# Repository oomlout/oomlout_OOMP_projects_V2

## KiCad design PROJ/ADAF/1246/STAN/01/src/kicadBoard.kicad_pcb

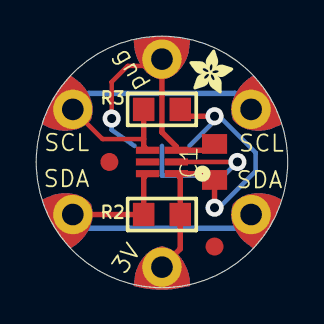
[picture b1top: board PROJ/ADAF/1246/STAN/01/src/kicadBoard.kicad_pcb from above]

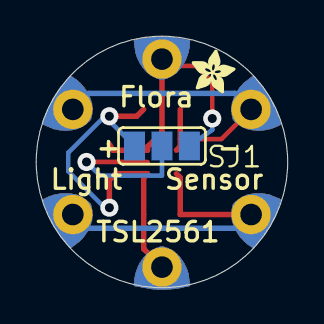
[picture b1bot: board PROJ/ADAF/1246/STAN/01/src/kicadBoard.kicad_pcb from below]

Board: 2 copper layers, 14.0 x 14.0 mm, 15 parts (2 on the bottom side), 5 nets.

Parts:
C1: 0.1uF; C0805K
FID1, FID2: FIDUCIAL""; FIDUCIAL_1MM
GND0: SEWTAP0.5IN; SEWINGTAP_0.5
R2, R3: 10K; _0805
SCL1, SCL2: SEWTAP0.5IN; SEWINGTAP_0.5
SDA1, SDA2: SEWTAP0.5IN; SEWINGTAP_0.5
SJ1: SJ_2
U2: TSL2561; TSL2561_FN
U$3, U$4: ADAFRUIT_2.5MM
VCC0: SEWTAP0.5IN; SEWINGTAP_0.5

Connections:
3.3V: C1.1, R2.2, R3.2, SJ1.3, U2.VDD, VCC0.TAP
ADDR: SJ1.2, U2.ADR
GND: C1.2, GND0.TAP, SJ1.1, U2.VSS
SCL: R3.1, SCL1.TAP, SCL2.TAP, U2.CLK
SDA: R2.1, SDA1.TAP, SDA2.TAP, U2.DATA

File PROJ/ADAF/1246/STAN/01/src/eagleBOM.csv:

"Part";"Value";"Device";"Package";"Description";"BOM";
"C1";"0.1uF";"C-USC0805K";"C0805K";"CAPACITOR, American symbol";"";
"FID1";"FIDUCIAL""";"FIDUCIAL""";"FIDUCIAL_1MM";"Fiducial Alignment Points";"EXCLUDE";
"FID2";"FIDUCIAL""";"FIDUCIAL""";"FIDUCIAL_1MM";"Fiducial Alignment Points";"EXCLUDE";
"GND";"SEWTAP0.5IN";"SEWTAP0.5IN";"SEWINGTAP_0.5";"";"";
"R2";"10K";"RESISTOR_0805";"_0805";"Resistors";"";
"R3";"10K";"RESISTOR_0805";"_0805";"Resistors";"";
"SCL1";"SEWTAP0.5IN";"SEWTAP0.5IN";"SEWINGTAP_0.5";"";"";
"SCL2";"SEWTAP0.5IN";"SEWTAP0.5IN";"SEWINGTAP_0.5";"";"";
"SDA1";"SEWTAP0.5IN";"SEWTAP0.5IN";"SEWINGTAP_0.5";"";"";
"SDA2";"SEWTAP0.5IN";"SEWTAP0.5IN";"SEWINGTAP_0.5";"";"";
"SJ1";"";"SJ2W";"SJ_2";"SMD solder JUMPER";"";
"U2";"TSL2561";"TSL2561";"TSL2561_FN";"TSL2561 Light-To-Digital Sensor";"";
"VCC";"SEWTAP0.5IN";"SEWTAP0.5IN";"SEWINGTAP_0.5";"";"";

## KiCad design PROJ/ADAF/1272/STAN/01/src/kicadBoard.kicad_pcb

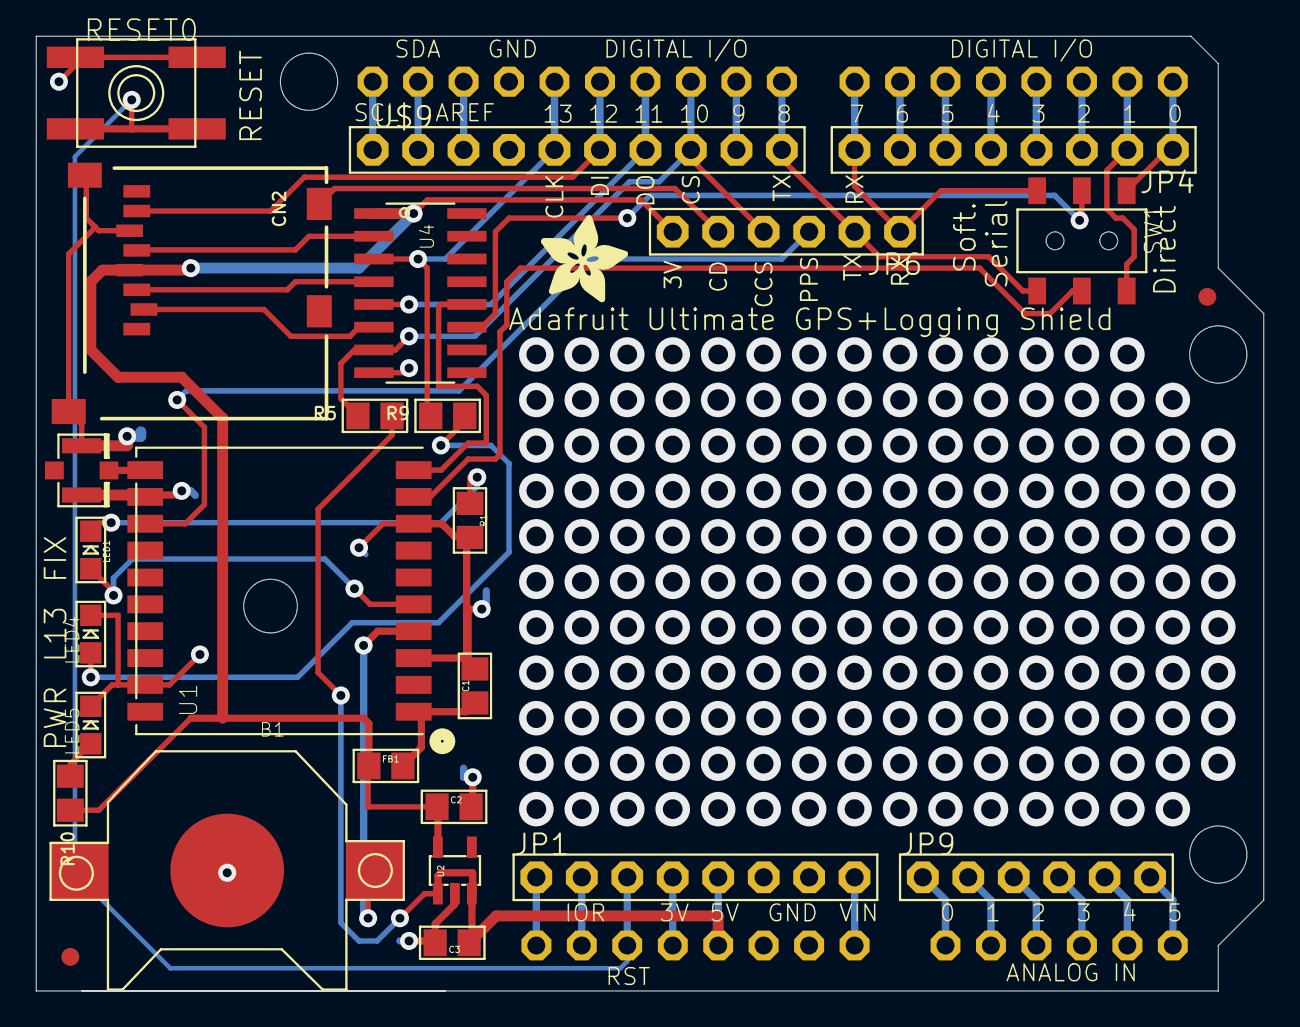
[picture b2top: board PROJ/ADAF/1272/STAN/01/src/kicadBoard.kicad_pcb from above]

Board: 2 copper layers, 68.6 x 53.3 mm, 32 parts (1 on the bottom side), 46 nets.

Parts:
@HOLE0, @HOLE1, @HOLE2: (no value)
B1: CR1220
C1: 0.1uF; 0805@1
C2, C3: 10uF; 0805@1
CN2: MICROSD
FB1: Ferrite; 0805@1
FID1, FID2: FIDUCIAL""; FIDUCIAL_1MM
JP1, JP4: D0-D7; 1X08-BIG
JP6, JP9: 1X06-BIG
LED1: red; CHIPLED_0805
LED4: yellow; CHIPLED_0805
LED5: green; CHIPLED_0805
R1: 1K; 0805
R5: 10K; 0805
R9, R10: 1k; 0805
RESET0: Reset; EVQ-Q2
SW1: EG1390
U1: FGPMMOPA6H
U2: MIC5225-3.3; SOT23-5
U3: ARDUINOR3-DIMENSION; ARDUINOR3
U4: 4050; SOIC16
U$9: PINHD-1X10; 1X10-BIG
U$13: ADAFRUIT_5MM
U$15: ADAFRUIT_TEXT_30MM
U$20: U.FL

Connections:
1PPS: JP6.3, U1.P$13
3.3V: C2.1, CN2.4, FB1.1, JP6.6, R10.2, U2.5, U4.1
+5V: C3.1, JP1.5, R5.1, U2.1, U2.3, U3.5V
FIX: LED1.A, U1.P$5
GND: B1.-, C1.2, C2.2, C3.2, CN2.6, CN2.MT1, CN2.MT2, JP1.6, JP1.7, LED4.C, LED5.C, R1.1, RESET0.B, RESET0.B', U1.P$3, U1.P$8, U1.P$12, U1.P$19, U2.2, U3.GND, U3.GND1, U3.GND2, U4.8, U$9.4, U$20.P$1, U$20.P$2
MISO: CN2.7, U3.D12, U$9.6
MOSI: U3.D11, U4.5, U$9.7
unnamed: C1.1, FB1.2, U1.P$1
unnamed: LED1.C, R1.2
unnamed: JP1.1, U3.RESERVED
unnamed: U1.P$11, U$20.P$3
unnamed: JP1.2, U3.IOREF
unnamed: JP1.4, U3.3V
unnamed: U3.SCL, U$9.1
unnamed: LED4.A, R9.1
unnamed: JP9.6, U3.A5
unnamed: JP9.5, U3.A4
unnamed: JP4.8, JP6.1, SW1.S2, U3.D7
unnamed: U3.SDA, U$9.2
unnamed: JP6.2, SW1.S1, U3.D8, U$9.10
unnamed: JP4.2, SW1.O1, U3.D1
unnamed: JP1.8, U3.VIN
unnamed: JP4.3, U3.D2
unnamed: JP4.4, U3.D3
unnamed: JP4.5, U3.D4
unnamed: JP4.6, U3.D5
unnamed: JP4.7, U3.D6
unnamed: U3.AREF, U$9.3
unnamed: U3.D9, U$9.9
unnamed: LED5.A, R10.1
unnamed: JP9.1, U3.A0
unnamed: JP9.2, U3.A1
unnamed: JP9.3, U3.A2
unnamed: JP9.4, U3.A3
unnamed: JP4.1, SW1.O2, U3.D0
RESET: JP1.3, RESET0.A, RESET0.A', U3.RESET
RX: U1.P$10, U4.12
RX_5V: SW1.P2, U4.11
SCK: R9.2, U3.D13, U4.3, U$9.5
SD_CD: CN2.CD1, JP6.5
SD_CS: JP6.4, R5.2, U3.D10, U4.7, U$9.8
SD_CSIN: CN2.2, U4.6
SD_DATAIN: CN2.3, U4.4
SD_SCKIN: CN2.5, U4.2
TX: SW1.P1, U1.P$9
VBACKUP: B1.+$1, U1.P$4

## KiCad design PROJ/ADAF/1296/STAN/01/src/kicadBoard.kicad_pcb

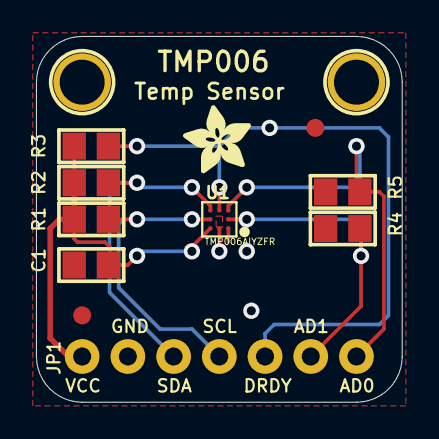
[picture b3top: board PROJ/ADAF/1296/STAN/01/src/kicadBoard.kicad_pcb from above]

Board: 2 copper layers, 20.3 x 20.3 mm, 13 parts (0 on the bottom side), 7 nets.

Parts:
C1: 10uF; 0805
FID1, FID2: FIDUCIAL""; FIDUCIAL_1MM
JP1: 1X07_ROUND_76
R1, R2, R3, R4, R5: 10K; 0805
U1: TMP006AIYZFR; WCSP-8
U$6, U$7: MOUNTINGHOLE2.5; MOUNTINGHOLE_2.5_PLATED
U$9: ADAFRUIT_3.5MM

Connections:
ADDR0: JP1.7, R5.2, U1.C1
ADDR1: JP1.6, R4.2, U1.B1
DRDY: JP1.5, R3.1, U1.C2
GND: C1.2, JP1.2, R4.1, R5.1, U1.A1, U1.A2
SCL: JP1.4, R1.1, U1.B3
SDA: JP1.3, R2.1, U1.C3
VCC: C1.1, JP1.1, R1.2, R2.2, R3.2, U1.A3

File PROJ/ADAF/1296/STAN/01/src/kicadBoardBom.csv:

"Id";"Designator";"Package";"Quantity";"Designation";"Supplier and ref";
1;"R4,R5,R2,R3,R1";"0805";5;"10K";;;
2;"U1";"WCSP-8";1;"TMP006AIYZFR";;;
3;"U$6,U$7";"MOUNTINGHOLE_2.5_PLATED";2;"MOUNTINGHOLE2.5";;;
4;"JP1";"1X07_ROUND_76";1;"";;;
5;"C1";"0805";1;"10uF";;;
6;"FID1,FID2";"FIDUCIAL_1MM";2;"FIDUCIAL""";;;
7;"U$9";"ADAFRUIT_3.5MM";1;"";;;

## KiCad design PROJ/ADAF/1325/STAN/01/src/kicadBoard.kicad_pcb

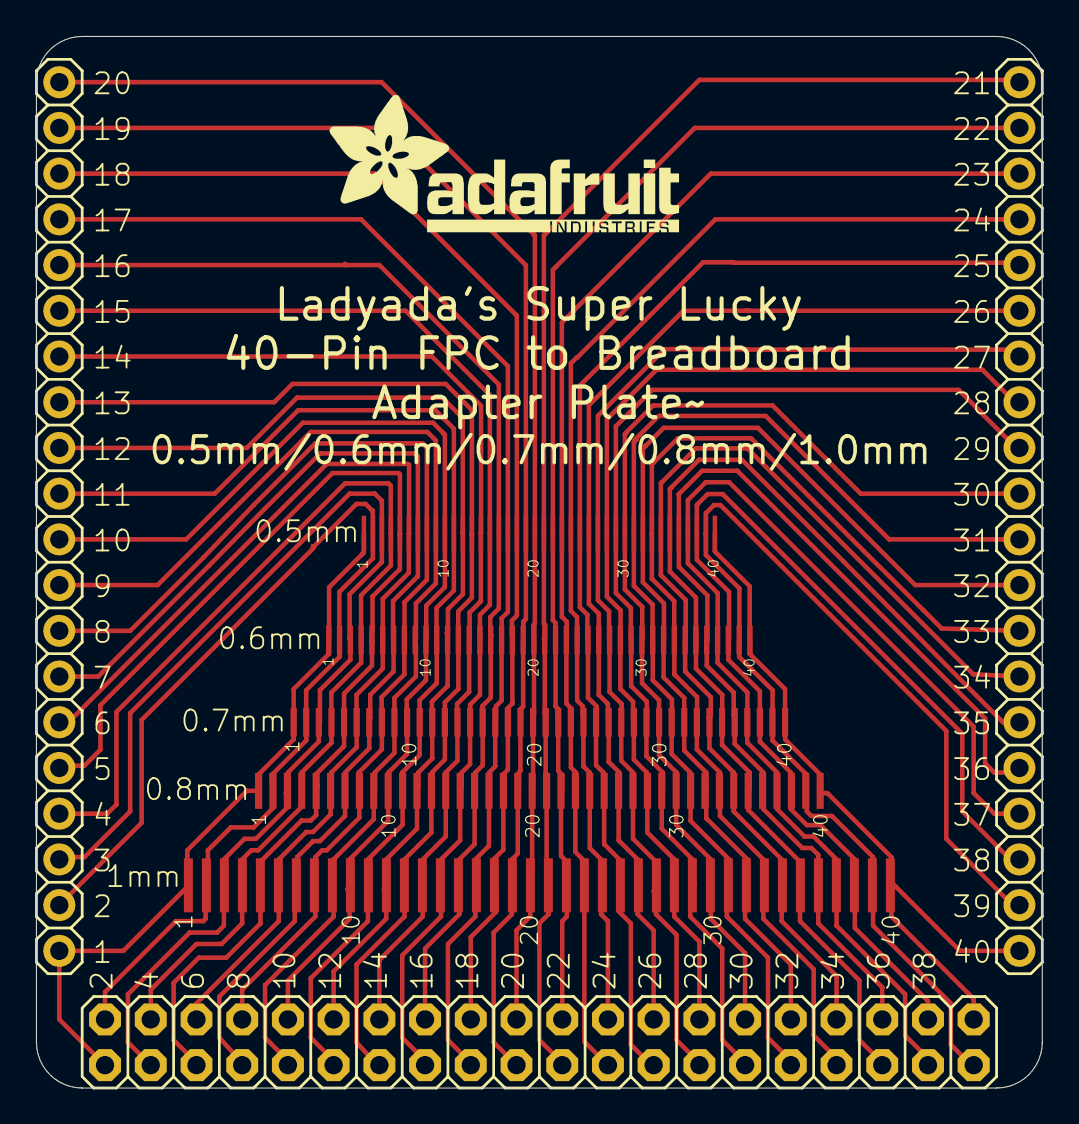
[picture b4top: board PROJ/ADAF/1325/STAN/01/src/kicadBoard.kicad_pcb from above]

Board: 16 copper layers, 55.9 x 58.4 mm, 9 parts (0 on the bottom side), 40 nets.

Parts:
CON1: PINHD-1X40-0.5MM; 1X40-0.5MM
JP1: 2X20-BIG
JP2, JP3: 1X20-BIG
U$1: PINHD-1X40-0.6MM; 1X40-0.6MM
U$2: PINHD-1X40-0.7MM; 1X40-0.7MM
U$3: PINHD-1X40-0.8MM; 1X40-0.8MM
U$4: PINHD-1X40-1MM; 1X40-1MM
U$5: ADAFRUIT_TEXT_20MM

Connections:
unnamed: CON1.1, JP1.1, JP2.1, U$1.1, U$2.1, U$3.1, U$4.1
unnamed: CON1.2, JP1.2, JP2.2, U$1.2, U$2.2, U$3.2, U$4.2
unnamed: CON1.3, JP1.3, JP2.3, U$1.3, U$2.3, U$3.3, U$4.3
unnamed: CON1.4, JP1.4, JP2.4, U$1.4, U$2.4, U$3.4, U$4.4
unnamed: CON1.5, JP1.5, JP2.5, U$1.5, U$2.5, U$3.5, U$4.5
unnamed: CON1.6, JP1.6, JP2.6, U$1.6, U$2.6, U$3.6, U$4.6
unnamed: CON1.7, JP1.7, JP2.7, U$1.7, U$2.7, U$3.7, U$4.7
unnamed: CON1.8, JP1.8, JP2.8, U$1.8, U$2.8, U$3.8, U$4.8
unnamed: CON1.9, JP1.9, JP2.9, U$1.9, U$2.9, U$3.9, U$4.9
unnamed: CON1.10, JP1.10, JP2.10, U$1.10, U$2.10, U$3.10, U$4.10
unnamed: CON1.11, JP1.11, JP2.11, U$1.11, U$2.11, U$3.11, U$4.11
unnamed: CON1.12, JP1.12, JP2.12, U$1.12, U$2.12, U$3.12, U$4.12
unnamed: CON1.13, JP1.13, JP2.13, U$1.13, U$2.13, U$3.13, U$4.13
unnamed: CON1.14, JP1.14, JP2.14, U$1.14, U$2.14, U$3.14, U$4.14
unnamed: CON1.15, JP1.15, JP2.15, U$1.15, U$2.15, U$3.15, U$4.15
unnamed: CON1.16, JP1.16, JP2.16, U$1.16, U$2.16, U$3.16, U$4.16
unnamed: CON1.17, JP1.17, JP2.17, U$1.17, U$2.17, U$3.17, U$4.17
unnamed: CON1.18, JP1.18, JP2.18, U$1.18, U$2.18, U$3.18, U$4.18
unnamed: CON1.19, JP1.19, JP2.19, U$1.19, U$2.19, U$3.19, U$4.19
unnamed: CON1.20, JP1.20, JP2.20, U$1.20, U$2.20, U$3.20, U$4.20
unnamed: CON1.21, JP1.21, JP3.1, U$1.21, U$2.21, U$3.21, U$4.21
unnamed: CON1.22, JP1.22, JP3.2, U$1.22, U$2.22, U$3.22, U$4.22
unnamed: CON1.23, JP1.23, JP3.3, U$1.23, U$2.23, U$3.23, U$4.23
unnamed: CON1.24, JP1.24, JP3.4, U$1.24, U$2.24, U$3.24, U$4.24
unnamed: CON1.25, JP1.25, JP3.5, U$1.25, U$2.25, U$3.25, U$4.25
unnamed: CON1.26, JP1.26, JP3.6, U$1.26, U$2.26, U$3.26, U$4.26
unnamed: CON1.27, JP1.27, JP3.7, U$1.27, U$2.27, U$3.27, U$4.27
unnamed: CON1.28, JP1.28, JP3.8, U$1.28, U$2.28, U$3.28, U$4.28
unnamed: CON1.29, JP1.29, JP3.9, U$1.29, U$2.29, U$3.29, U$4.29
unnamed: CON1.30, JP1.30, JP3.10, U$1.30, U$2.30, U$3.30, U$4.30
unnamed: CON1.31, JP1.31, JP3.11, U$1.31, U$2.31, U$3.31, U$4.31
unnamed: CON1.32, JP1.32, JP3.12, U$1.32, U$2.32, U$3.32, U$4.32
unnamed: CON1.33, JP1.33, JP3.13, U$1.33, U$2.33, U$3.33, U$4.33
unnamed: CON1.34, JP1.34, JP3.14, U$1.34, U$2.34, U$3.34, U$4.34
unnamed: CON1.35, JP1.35, JP3.15, U$1.35, U$2.35, U$3.35, U$4.35
unnamed: CON1.36, JP1.36, JP3.16, U$1.36, U$2.36, U$3.36, U$4.36
unnamed: CON1.37, JP1.37, JP3.17, U$1.37, U$2.37, U$3.37, U$4.37
unnamed: CON1.38, JP1.38, JP3.18, U$1.38, U$2.38, U$3.38, U$4.38
unnamed: CON1.39, JP1.39, JP3.19, U$1.39, U$2.39, U$3.39, U$4.39
unnamed: CON1.40, JP1.40, JP3.20, U$1.40, U$2.40, U$3.40, U$4.40

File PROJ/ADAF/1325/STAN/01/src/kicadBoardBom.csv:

"Id";"Designator";"Package";"Quantity";"Designation";"Supplier and ref";
1;"JP3,JP2";"1X20-BIG";2;"";;;
2;"U$2";"1X40-0.7MM";1;"PINHD-1X40-0.7MM";;;
3;"CON1";"1X40-0.5MM";1;"PINHD-1X40-0.5MM";;;
4;"U$1";"1X40-0.6MM";1;"PINHD-1X40-0.6MM";;;
5;"U$5";"ADAFRUIT_TEXT_20MM";1;"";;;
6;"U$4";"1X40-1MM";1;"PINHD-1X40-1MM";;;
7;"JP1";"2X20-BIG";1;"";;;
8;"U$3";"1X40-0.8MM";1;"PINHD-1X40-0.8MM";;;

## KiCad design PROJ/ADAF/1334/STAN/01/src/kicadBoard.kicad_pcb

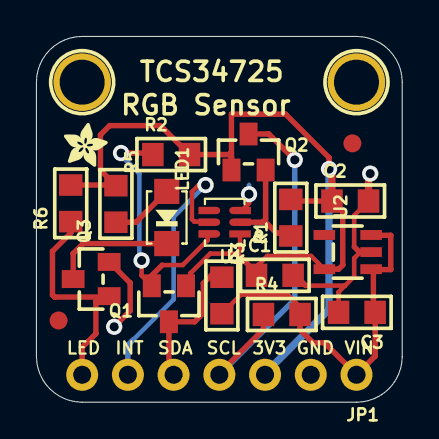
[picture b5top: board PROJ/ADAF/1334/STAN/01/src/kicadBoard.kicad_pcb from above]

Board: 2 copper layers, 20.3 x 20.3 mm, 22 parts (1 on the bottom side), 11 nets.

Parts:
C1: 0.1µF; _0805
C2, C3: 10µF; _0805
FID1, FID2: FIDUCIAL""; FIDUCIAL_1MM
JP1: 1X07_ROUND_70
LED1: 45-21/LK2C-B38452C4CB2/2T; EVERLIGHT_45-21
Q1, Q2, Q3: BSS138; SOT23-WIDE
R1, R2, R3, R4, R6: 10K; _0805
R5: TBD; _0805
U1: TCS34725; TCS3472_FN6
U2: RT9193; SOT23-5
U$2: ADAFRUIT_2.5MM
U$8, U$14: MOUNTINGHOLE2.5; MOUNTINGHOLE_2.5_PLATED
U$18: ADAFRUIT_5MM

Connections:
+3V3: C1.1, C2.1, JP1.3, Q1.1, Q2.1, R1.2, R2.2, R5.1, R6.2, U1.P$1, U2.5
GND: C1.2, C2.2, C3.2, JP1.2, Q3.2, U1.P$3, U2.2
INT: JP1.6, U1.P$5
LED_EN: JP1.7, Q3.1, R6.1
unnamed: LED1.K, Q3.3
unnamed: LED1.A, R5.2
SCL_3V: Q2.2, R1.1, U1.P$2
SCL_5V: JP1.4, Q2.3, R4.1
SDA_3V: Q1.2, R2.1, U1.P$6
SDA_5V: JP1.5, Q1.3, R3.1
VIN: C3.1, JP1.1, R3.2, R4.2, U2.1, U2.3
